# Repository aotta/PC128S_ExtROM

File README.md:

# PC128S_ExtROM
kicad project for an external Rom for Olivetti Prodest PC128S
For further info, search on stardot.co.uk forum

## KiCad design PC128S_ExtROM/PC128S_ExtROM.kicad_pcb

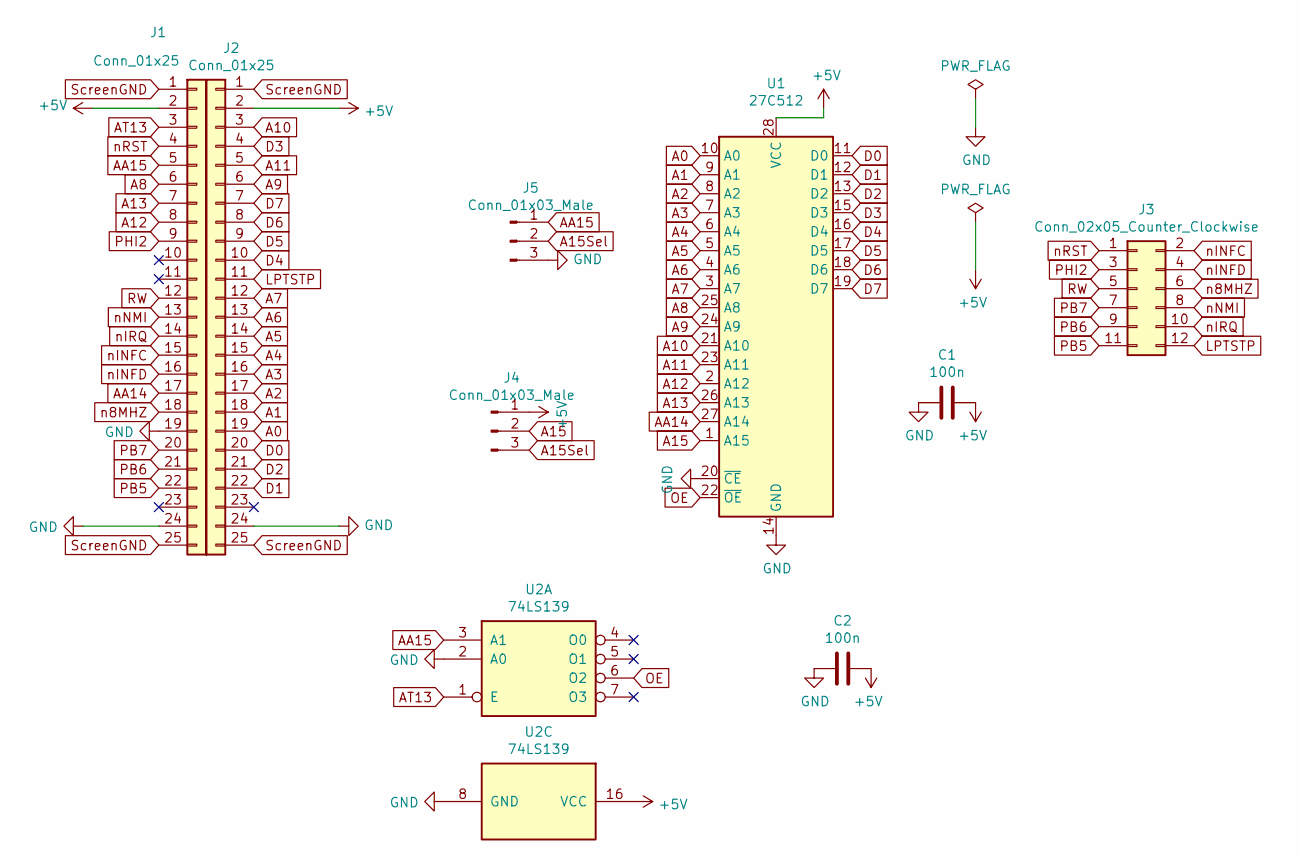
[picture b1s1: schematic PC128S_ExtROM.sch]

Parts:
C1, C2: 100n; C_Disc_D5.0mm_W2.5mm_P5.00mm
J1, J2: Conn_01x25; PinHeader_1x25_P2.54mm_Vertical
J3: Conn_02x05_Counter_Clockwise; PinHeader_2x06_P2.54mm_Vertical
J4, J5: Conn_01x03_Male; PinSocket_1x03_P2.54mm_Vertical
U1: 27C512; DIP-28_W15.24mm
U2: 74LS139; DIP-16_W7.62mm_Socket

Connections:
+5V: C1.1, C2.1, J1.2, J2.2, J4.1, U1.28 (VCC), U2.16 (VCC)
A0: J2.19, U1.10 (A0)
A1: J2.18, U1.9 (A1)
A2: J2.17, U1.8 (A2)
A3: J2.16, U1.7 (A3)
A4: J2.15, U1.6 (A4)
A5: J2.14, U1.5 (A5)
A6: J2.13, U1.4 (A6)
A7: J2.12, U1.3 (A7)
A8: J1.6, U1.25 (A8)
A9: J2.6, U1.24 (A9)
A10: J2.3, U1.21 (A10)
A11: J2.5, U1.23 (A11)
A12: J1.8, U1.2 (A12)
A13: J1.7, U1.26 (A13)
A15: J4.2, U1.1 (A15)
A15Sel: J4.3, J5.2
AA14: J1.17, U1.27 (A14)
AA15: J1.5, J5.1, U2.3 (A1)
AT13: J1.3, U2.1 (E)
D0: J2.20, U1.11 (D0)
D1: J2.22, U1.12 (D1)
D2: J2.21, U1.13 (D2)
D3: J2.4, U1.15 (D3)
D4: J2.10, U1.16 (D4)
D5: J2.9, U1.17 (D5)
D6: J2.8, U1.18 (D6)
D7: J2.7, U1.19 (D7)
GND: C1.2, C2.2, J1.19, J1.24, J2.24, J5.3, U1.14 (GND), U1.20 (~CE), U2.2 (A0), U2.8 (GND)
LPTSTP: J2.11, J3.12
OE: U1.22 (~OE), U2.6 (O2)
PB5: J1.22, J3.11
PB6: J1.21, J3.9
PB7: J1.20, J3.7
PHI2: J1.9, J3.3
RW: J1.12, J3.5
ScreenGND: J1.1, J1.25, J2.1, J2.25
n8MHZ: J1.18, J3.6
nINFC: J1.15, J3.2
nINFD: J1.16, J3.4
nIRQ: J1.14, J3.10
nNMI: J1.13, J3.8
nRST: J1.4, J3.1

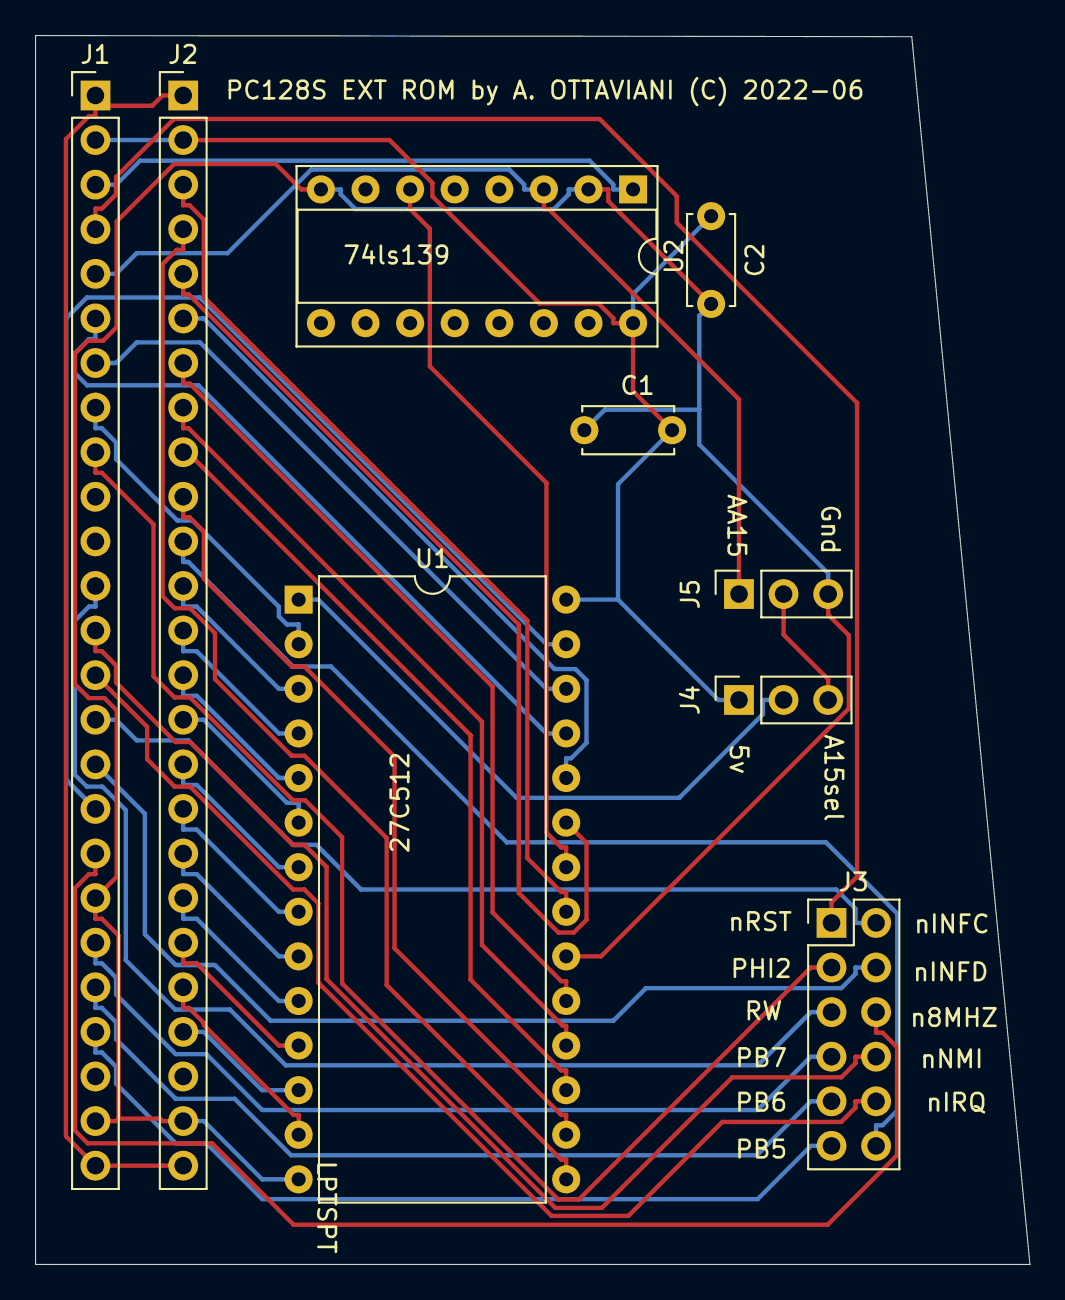
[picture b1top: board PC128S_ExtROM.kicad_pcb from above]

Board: 2 copper layers, 56.6 x 70.0 mm, 9 parts (0 on the bottom side), 43 nets.

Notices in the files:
PC128S_ExtROM/PC128S_ExtROM.kicad_pcb:
PC128S EXT ROM by A. OTTAVIANI (C) 2022-06
